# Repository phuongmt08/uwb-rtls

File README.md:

<div align="center">

# UWB-RTLS

### On-device indoor positioning for autonomous mobile robots

**[Results](#experimental-validation) · [System](#system-overview) · [Features](#core-capabilities) · [Quick start](#quick-start) · [Documentation](#documentation)**

</div>

UWB-RTLS is an end-to-end real-time location system developed for indoor mobile robots. Fixed UWB Anchors measure their distance to a mobile Tag using DS-TWR. The Tag validates the ranges, selects a reliable Anchor subset, fuses UWB with IMU data, and calculates its pose directly on an STM32F411. RTLS Studio provides wireless configuration, live diagnostics, visualization, and experiment logging.

<table>
  <tr>
    <th align="center">Best evaluated MAE</th>
    <th align="center">Best evaluated RMSE</th>
    <th align="center">Positioning</th>
    <th align="center">Validation</th>
  </tr>
  <tr>
    <td align="center"><strong>8.5 cm</strong></td>
    <td align="center"><strong>10.9 cm</strong></td>
    <td align="center"><strong>On the Tag</strong></td>
    <td align="center"><strong>2 real environments</strong></td>
  </tr>
</table>

## System Overview

Fixed Anchors provide UWB references around the operating area. The mobile Tag performs ranging and position estimation, sends pose data directly to the vehicle controller, and exposes configuration and telemetry through the BLE gateway.

```mermaid
flowchart TD
    Anchors["Fixed UWB Anchors"] <-->|"DS-TWR ranging"| Tag["Mobile Tag<br/>On-device positioning"]
    Tag -->|"Pose over USB"| Robot["Vehicle Controller"]
    Tag <-->|"Configuration + telemetry"| Gateway["BLE Gateway"]
    Gateway <-->|"USB serial"| Studio["RTLS Studio"]
```

Positioning remains operational without the desktop application: RTLS Studio is a configuration and observability tool, not the positioning engine.

## System in Practice

The experimental platform uses the developed Anchor/Tag hardware and a 1:10-scale vehicle. The photographs below show the actual Chapter 5 test-yard deployment.

<p align="center">
  <br>
  <sub>Full four-Anchor test-yard deployment</sub>
</p>

<table>
  <tr>
    <td width="50%" align="center"><br><sub>Anchor installed at the surveyed height</sub></td>
    <td width="50%" align="center"><br><sub>1:10-scale vehicle carrying the Tag</sub></td>
  </tr>
</table>

RTLS Studio provides the host-side view of the deployed system for device configuration, diagnostics, and experiment recording.

<p align="center">
  <br>
  <sub>Connected-device diagnostics, live logs, and recorded ranging sessions</sub>
</p>

## Experimental Validation

Two dynamic cases were evaluated: a large, mostly line-of-sight test yard and a furnished classroom with stronger multipath and partial obstruction. Direct trilateration and UKF outputs were recorded simultaneously so both estimators saw the same motion and UWB measurements.

### Evaluation protocol

| Item | Method |
|---|---|
| Reference path | Manually surveyed control points connected by interpolation |
| Point error | Euclidean distance from each estimate to the nearest point on the reference path |
| Active interval | Samples before departure and after the vehicle stopped were excluded |
| Repetition | Three runs for each trajectory or Anchor configuration |
| Reported metrics | MAE, RMSE, 95th-percentile error, and maximum error |

### Case 1 — Test yard, four Anchors

The first case used a **9.76 m × 11.64 m** indoor test yard with mostly clear line of sight. Four Anchors surrounded the working area at **0.895 m**, while the Tag was mounted at **0.350 m**. The vehicle followed two surveyed trajectories, each repeated three times.

<table>
  <tr>
    <td width="50%" align="center"></td>
    <td width="50%" align="center"></td>
  </tr>
  <tr>
    <td align="center"><sub>Reference path, direct trilateration, and UKF trajectory</sub></td>
    <td align="center"><sub>Position error from the same representative run</sub></td>
  </tr>
</table>

| Estimator | MAE (m) | RMSE (m) | P95 (m) | Max (m) |
|---|---:|---:|---:|---:|
| Direct trilateration | 0.102 ± 0.006 | 0.134 ± 0.010 | 0.268 ± 0.024 | 0.782 ± 0.281 |
| **UKF** | **0.091 ± 0.005** | **0.117 ± 0.005** | **0.236 ± 0.014** | **0.456 ± 0.063** |

Across the test-yard runs, the UKF reduced average MAE by **10.9%**, RMSE by **12.8%**, and maximum error from **0.782 m to 0.456 m**.

### Case 2 — Classroom, four and six Anchors

The second case used an **8.3 m × 8.7 m** classroom containing desks, people, and reflective surfaces. Anchors were installed at **2.495 m** and the Tag at **0.585 m**. Both four- and six-Anchor layouts were tested to measure the value of additional spatial redundancy.

<table>
  <tr>
    <td width="50%" align="center"></td>
    <td width="50%" align="center"></td>
  </tr>
  <tr>
    <td align="center"><sub>Wall-mounted Anchor</sub></td>
    <td align="center"><sub>Classroom deployment with furniture and occupants</sub></td>
  </tr>
</table>

<table>
  <tr>
    <td width="50%" align="center"></td>
    <td width="50%" align="center"></td>
  </tr>
  <tr>
    <td align="center"><sub>Six-Anchor reference, trilateration, and UKF trajectories</sub></td>
    <td align="center"><sub>Position error from the same representative run</sub></td>
  </tr>
</table>

| Layout | Estimator | MAE (m) | RMSE (m) | P95 (m) | Max (m) |
|---|---|---:|---:|---:|---:|
| 4 Anchors | Direct trilateration | 0.173 ± 0.027 | 0.230 ± 0.037 | 0.457 ± 0.084 | 1.099 ± 0.131 |
| 4 Anchors | **UKF** | **0.139 ± 0.036** | **0.185 ± 0.043** | **0.393 ± 0.085** | **0.583 ± 0.064** |
| 6 Anchors | Direct trilateration | 0.123 ± 0.006 | 0.177 ± 0.007 | 0.340 ± 0.035 | 1.150 ± 0.562 |
| 6 Anchors | **UKF** | **0.085 ± 0.013** | **0.109 ± 0.015** | **0.215 ± 0.035** | **0.340 ± 0.026** |

The six-Anchor UKF configuration produced the strongest overall result: **8.5 cm MAE**, **10.9 cm RMSE**, **21.5 cm P95**, and **34.0 cm maximum error**. The result demonstrates the benefit of additional valid ranging links in a difficult indoor environment.

> **Measurement scope:** the reference trajectory was reconstructed from manually measured control points, not an independent motion-capture system. The results therefore quantify tracking performance under the documented procedure rather than metrology-grade absolute accuracy.

## Core Capabilities

| Area | Implemented capability | Purpose |
|---|---|---|
| Ranging | Asymmetric DS-TWR with TDMA scheduling | Measures multiple Tag-to-Anchor ranges without clock synchronization |
| Measurement validation | Spatial innovation prefilter | Rejects inconsistent range combinations before estimation |
| Anchor selection | Robust precision and WGDOP ranking | Chooses a geometrically useful three-Anchor measurement set |
| Sensor fusion | 8-state UWB/IMU UKF | Estimates planar position, velocity, yaw, and IMU biases |
| Embedded runtime | FreeRTOS task-based firmware | Separates ranging, fusion, communication, storage, and supervision |
| Hardware flexibility | Unified Tag/Anchor STM32 firmware | Selects the device role and Anchor identity without maintaining separate applications |
| Configuration | Persistent profiles with CRC-protected storage | Keeps deployment parameters across resets |
| Communication | Shared Protobuf messages with COBS-framed transport | Maintains one contract across STM32, BLE, and Python |
| Desktop tooling | RTLS Studio and firmware programmer | Supports commissioning, live diagnostics, logs, and updates |

## Hardware and Software

| Layer | Main technology | Responsibility |
|---|---|---|
| Tag and Anchor MCU | STM32F411CEU6, Cortex-M4F | Real-time protocol, positioning, sensor fusion, and interfaces |
| UWB radio | Decawave/Qorvo DW1000 module | Precision packet timestamping for DS-TWR |
| Motion sensor | 6-DOF SPI IMU | Acceleration and yaw-rate input to the UKF |
| BLE nodes | Nordic nRF52 | Wireless configuration and telemetry |
| USB gateway | Nordic nRF52840 dongle | BLE central and USB bridge |
| Embedded OS | FreeRTOS | Deterministic task and queue organization |
| Desktop | Python 3.10+ and PyQt6 | RTLS Studio, programming, and analysis tools |

### Verified Development Environment

| Tool | Verified version |
|---|---|
| STM32CubeIDE | 1.19.0; project supports the 1.10+ workflow |
| Arm GNU Toolchain | 10.3.1 and 13.3.Rel1 |
| GNU Make | 4.4.1 |
| Nordic nRF5 SDK | 17.1.0 |
| Python | 3.10+; 3.12 verified |

## Quick Start

The commands below build the repository and launch RTLS Studio. Device flashing, antenna-delay calibration, Anchor surveying, and commissioning are covered in the [Getting Started Guide](docs/getting_started.md) and [Deployment Guide](docs/deployment.md).

### 1. Clone and generate the shared protocol

```powershell
git clone --recursive https://github.com/phuongmt08/uwb-rtls.git
cd uwb-rtls
make -C protocol
```

### 2. Build the STM32 firmware

Install STM32CubeIDE or an Arm GNU toolchain, then point `GCC_PATH` to its compiler `bin` directory.

```powershell
$env:GCC_PATH = "C:\path\to\arm-none-eabi\bin"
make -C firmware/uwb -j8
```

The build produces ELF, HEX, and BIN files under `firmware/uwb/build`.

### 3. Build the BLE firmware when required

The gateway and BLE bridge targets use Nordic nRF5 SDK 17.1.0.

```powershell
$env:SDK_ROOT = "C:\nRF5_SDK_17.1.0_ddde5a0"
make -C firmware/ble_firmware/central/armgcc
make -C firmware/ble_firmware/peripheral/armgcc
```

### 4. Launch RTLS Studio

```powershell
cd software
python -m venv .venv
.\.venv\Scripts\Activate.ps1
pip install -r requirements.txt
python uwb_rtls_studio/main.py
```

### 5. Commission a deployment

1. Install at least four Anchors around the operating area and assign unique IDs.
2. Survey their coordinates and create the deployment profile in RTLS Studio.
3. Mount the Tag on the vehicle and enter the Tag height.
4. Connect the BLE gateway, select the Tag, and push the configuration.
5. Start ranging and confirm that at least three valid Anchor links are available.
6. Monitor the embedded pose or record a session for offline evaluation.

## Repository Structure

```text
uwb-rtls/
├── firmware/     STM32 application, BLE firmware, and bootloader
├── software/     RTLS Studio, programmer, and analysis tools
├── protocol/     Protobuf contracts and generated bindings
├── hardware/     Schematics, PCB sources, and calibration data
└── docs/         Setup, deployment, architecture, algorithms, and thesis
```

## Documentation

| Start here | Scope |
|---|---|
| **[Getting Started](docs/getting_started.md)** | Toolchains, builds, flashing, and first connection |
| **[Deployment and Commissioning](docs/deployment.md)** | Physical layout, Anchor survey, calibration, and validation |
| **[Firmware Architecture](docs/firmware/architecture.md)** | Embedded layers, RTOS tasks, queues, and runtime ownership |
| **[DS-TWR Ranging Protocol](docs/firmware/ranging_protocol.md)** | Packet sequence, timestamps, timing, and TDMA behavior |
| **[Positioning Algorithms](docs/firmware/positioning_algorithms.md)** | Mathematical model, prefilter, Anchor selection, and UKF |
| **[Schematics and Specifications](docs/hardware/schematics_and_specs.md)** | Hardware boards, interfaces, and design references |
| **[RTLS Studio and Tools](docs/software/rtls_studio_and_tools.md)** | Desktop configuration, monitoring, logging, and programming |
| **[Thesis](docs/thesis/thesis_final.pdf)** | Full design, implementation, and experimental evaluation |

## Team

Developed at the **Faculty of Mechanical Engineering**, Ho Chi Minh City University of Technology and Engineering (**HCMUTE**).

- **Phuong Mai** — Firmware and system architecture
- **Dong Son** — Project co-developer
- **Trung Quan** — Project co-developer

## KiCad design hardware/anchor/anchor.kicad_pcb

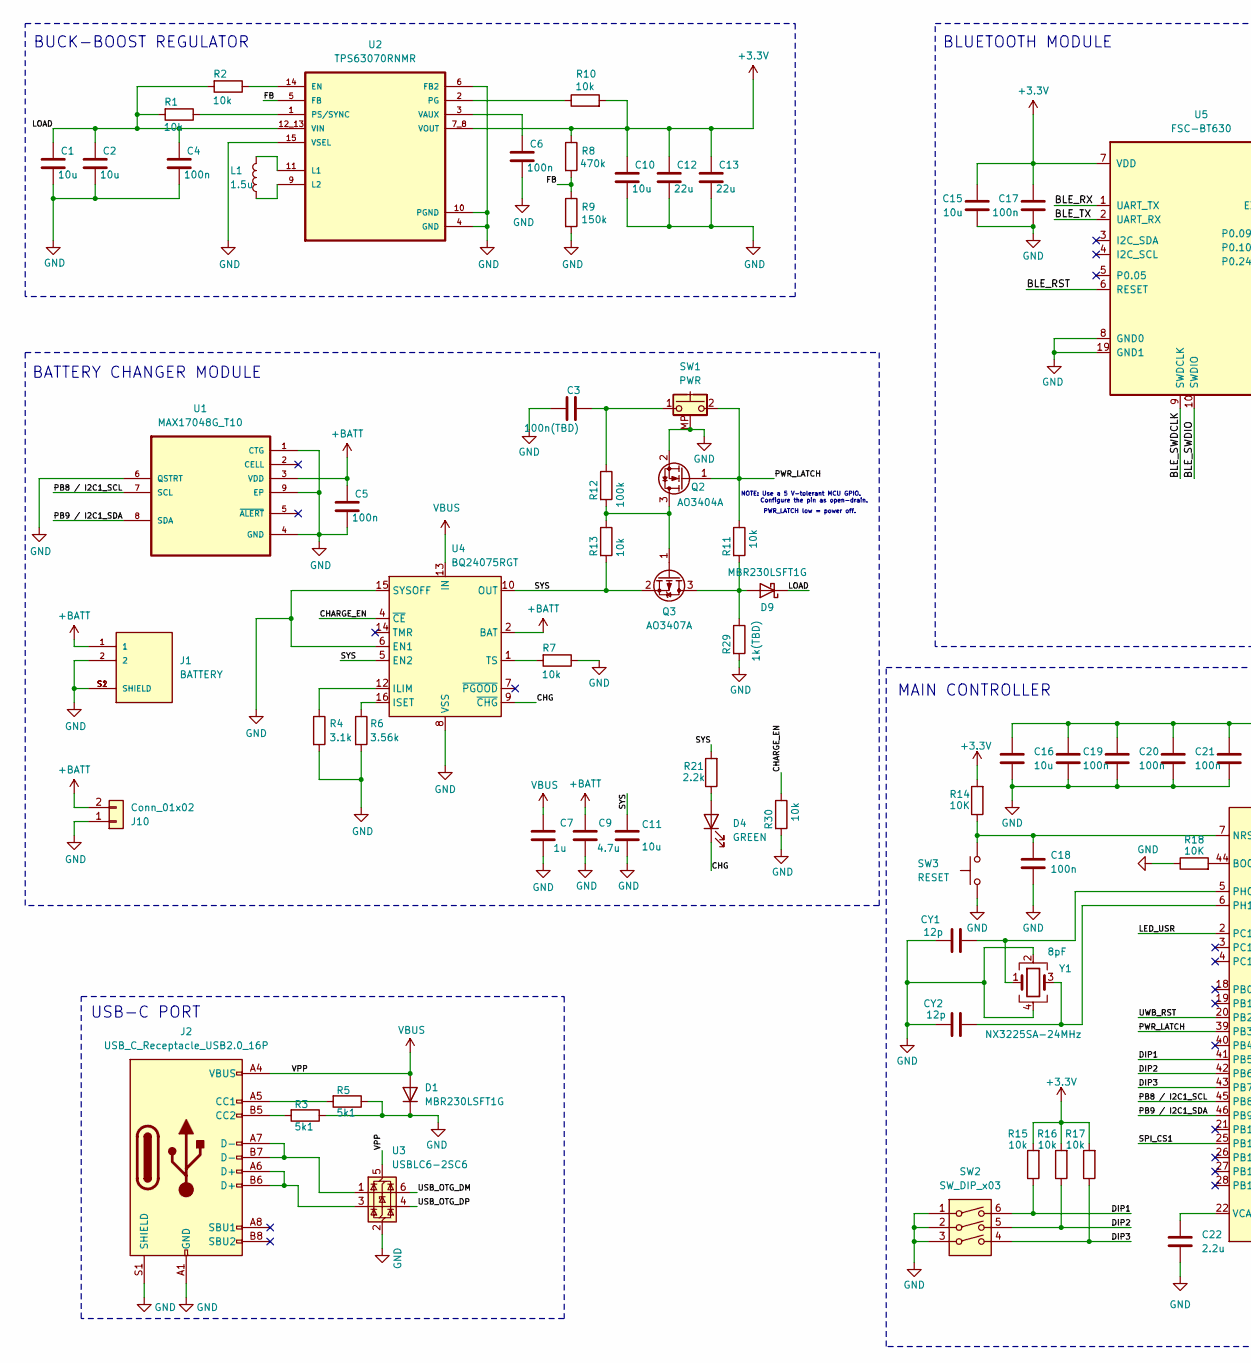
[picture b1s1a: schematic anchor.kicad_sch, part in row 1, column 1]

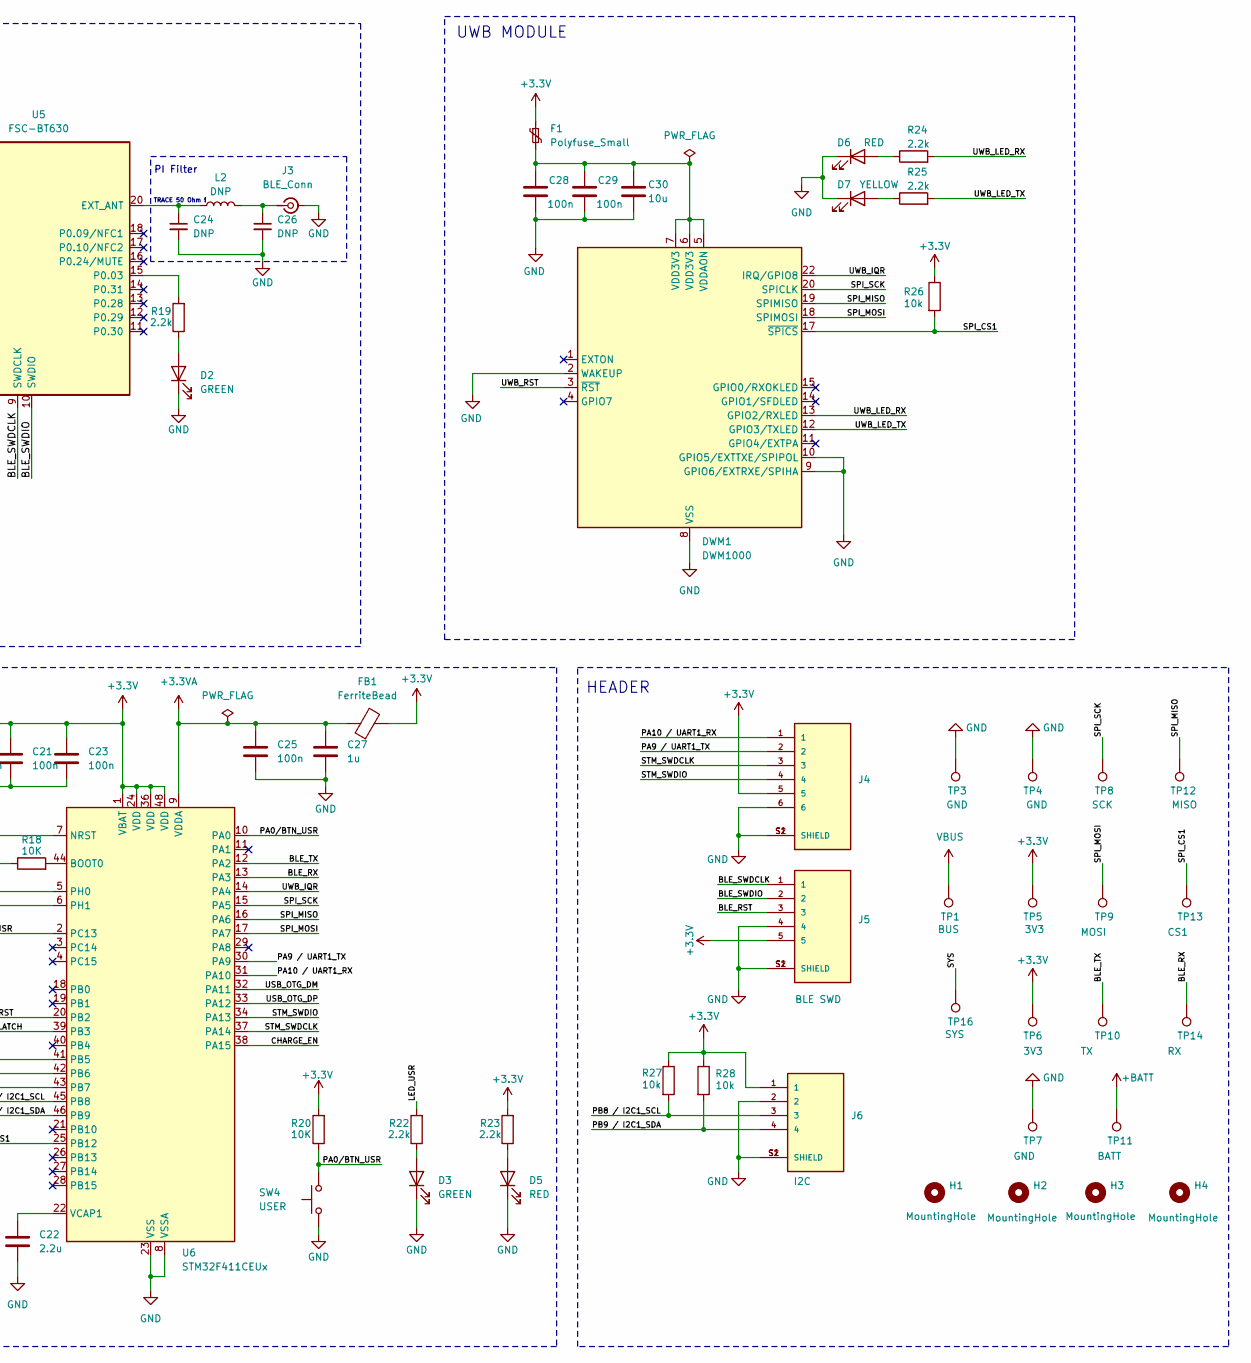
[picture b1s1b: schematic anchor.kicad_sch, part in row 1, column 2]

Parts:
C1, C2, C10, C11: 10u; C_0805_2012Metric
C3: 100n(TBD); C_0603_1608Metric
C4, C5, C6: 100n; C_0603_1608Metric
C7: 1u; C_0805_2012Metric
C9: 4.7u; C_0805_2012Metric
C12, C13: 22u; C_0805_2012Metric
C15, C16, C30: 10u; C_0805_2012Metric_Pad1.18x1.45mm_HandSolder
C17, C18, C19, C20, C21, C23, C25, C28, C29: 100n; C_0603_1608Metric_Pad1.08x0.95mm_HandSolder
C22: 2.2u; C_0805_2012Metric_Pad1.18x1.45mm_HandSolder
C24, C26: DNP; C_0402_1005Metric
C27: 1u; C_0805_2012Metric_Pad1.18x1.45mm_HandSolder
CY1, CY2: 12p; C_0603_1608Metric_Pad1.08x0.95mm_HandSolder
D1: MBR230LSFT1G; D_SOD-323
D2, D3, D4: GREEN; LED_0603_1608Metric_Pad1.05x0.95mm_HandSolder
D5, D6: RED; LED_0603_1608Metric_Pad1.05x0.95mm_HandSolder
D7: YELLOW; LED_0603_1608Metric_Pad1.05x0.95mm_HandSolder
D9: MBR230LSFT1G; D_SOD-123
DWM1: DWM1000
F1: Polyfuse_Small; Fuse_1206_3216Metric
FB1: FerriteBead; L_0603_1608Metric_Pad1.05x0.95mm_HandSolder
H1, H2, H3, H4: MountingHole; MountingHole_2.2mm_M2
J1: BATTERY; JST_BM02B-SRSS-TB_LF__SN_; PARTREV N/A
J2: USB_C_Receptacle_USB2.0_16P; USB_C_Receptacle_HRO_TYPE-C-31-M-12
J3: BLE_Conn; U.FL_Hirose_U.FL-R-SMT-1_Vertical
J4: BM06B-SRSS-TB_LF__SN_; JST_SH_BM06B-SRSS-TB_1x06-1MP_P1.00mm_Vertical; PARTREV N/A
J5: BLE SWD; JST_BM05B-SRSS-TB_LF__SN_; PARTREV N/A
J6: I2C; JST_BM04B-SRSS-TB_LF__SN_; PARTREV N/A
J10: Conn_01x02; SolderWire-0.1sqmm_1x02_P3.6mm_D0.4mm_OD1mm
L1: 1.5u; L_Sunlord_SWPA4020S
L2: DNP; L_0402_1005Metric
Q2: AO3404A; SOT-23
Q3: AO3407A; SOT-23
R1, R2, R7, R10, R11, R13, R30: 10k; R_0603_1608Metric
R3, R5: 5k1; R_0603_1608Metric_Pad0.98x0.95mm_HandSolder
R4: 3.1k; R_0603_1608Metric
R6: 3.56k; R_0603_1608Metric
R8: 470k; R_0805_2012Metric_Pad1.20x1.40mm_HandSolder
R9: 150k; R_0805_2012Metric_Pad1.20x1.40mm_HandSolder
R12: 100k; R_0603_1608Metric
R14, R18, R20: 10K; R_0603_1608Metric_Pad0.98x0.95mm_HandSolder
R15, R16, R17, R26, R27, R28: 10k; R_0603_1608Metric_Pad0.98x0.95mm_HandSolder
R19, R22, R23, R24, R25: 2.2k; R_0603_1608Metric_Pad0.98x0.95mm_HandSolder
R21: 2.2k; R_0603_1608Metric
R29: 1k(TBD); R_0603_1608Metric
SW1: PWR; SW_Push_1P1T-MP_NO_Horizontal_Alps_SKRTLAE010
SW2: SW_DIP_x03; SW_DIP_SPSTx03_Slide_KingTek_DSHP03TJ_W5.25mm_P1.27mm_JPin
SW3: RESET; SW_Tactile_SMD_3x4mm_2pin_update
SW4: USER; SW_Tactile_SMD_3x4mm_2pin_update
TP1: BUS; TestPoint_Pad_D1.5mm
TP3, TP7: GND; TestPoint_Pad_D1.5mm
TP4: GND; TestPoint_Pad_1.0x1.0mm
TP5, TP6: 3V3; TestPoint_Pad_D1.5mm
TP8: SCK; TestPoint_Pad_D1.0mm
TP9: MOSI; TestPoint_Pad_D1.0mm
TP10: TX; TestPoint_Pad_D1.0mm
TP11: BATT; TestPoint_Pad_D1.5mm
TP12: MISO; TestPoint_Pad_D1.0mm
TP13: CS1; TestPoint_Pad_D1.0mm
TP14: RX; TestPoint_Pad_D1.0mm
TP16: SYS; TestPoint_Pad_D1.5mm
U1: MAX17048G_T10; SON-8-1EP_3x2mm_P0.5mm_EP1.4x1.6mm
U2: TPS63070RNMR; VREG_TPS63070RNMR
U3: USBLC6-2SC6; SOT-23-6
U4: BQ24075RGT; VQFN-16-1EP_3x3mm_P0.5mm_EP1.6x1.6mm
U5: FSC-BT630
U6: STM32F411CEUx; QFN-48-1EP_7x7mm_P0.5mm_EP5.6x5.6mm
Y1: NX3225SA-24MHz; Crystal_SMD_3225-4Pin_3.2x2.5mm

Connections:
+3.3V: C10.1, C12.1, C13.1, C15.1, C16.1, C17.1, C19.1, C20.1, C21.1, C23.1, F1.1, FB1.2, J4.5, J5.5, J6.1, R8.1, R10.2, R14.2, R15.2, R16.2, R17.2, R20.2, R23.2, R26.1, R27.1, R28.1, TP5.1, TP6.1, U2.7_8 (VOUT), U5.7 (VDD), U6.1 (VBAT), U6.24 (VDD), U6.36 (VDD), U6.48 (VDD)
+3.3VA: C25.1, C27.1, FB1.1, U6.9 (VDDA)
+BATT: C5.1, C9.1, J1.1, J10.2, TP11.1, U1.3 (VDD), U4.2 (BAT), U4.3 (BAT)
/BLE_RST: J5.3, U5.6 (RESET)
/BLE_RX: TP14.1, U5.1 (UART_TX), U6.13 (PA3)
/BLE_SWDCLK: J5.1, U5.9 (SWDCLK)
/BLE_SWDIO: J5.2, U5.10 (SWDIO)
/BLE_TX: TP10.1, U5.2 (UART_RX), U6.12 (PA2)
/CHARGE_EN: R30.1, U4.4 (~CE), U6.38 (PA15)
/CHG: D4.1 (K), U4.9 (~CHG)
/DIP1: R15.1, SW2.6, U6.41 (PB5)
/DIP2: R16.1, SW2.5, U6.42 (PB6)
/DIP3: R17.1, SW2.4, U6.43 (PB7)
/FB: R8.2, R9.1, U2.5 (FB)
/LED_USR: R22.2, U6.2 (PC13)
/LOAD: C1.1, C2.1, C4.1, D9.1 (K), R1.2, R2.2, U2.12_13 (VIN)
/PA0/BTN_USR: R20.1, SW4.2, U6.10 (PA0)
/PA9 / UART1_TX: J4.2, U6.30 (PA9)
/PA10 / UART1_RX: J4.1, U6.31 (PA10)
/PB8 / I2C1_SCL: J6.3, R27.2, U1.7 (SCL), U6.45 (PB8)
/PB9 / I2C1_SDA: J6.4, R28.2, U1.8 (SDA), U6.46 (PB9)
/PWR_LATCH: Q2.1 (G), R11.1, SW1.2, U6.39 (PB3)
/SPI_CS1: DWM1.17 (~SPICS), R26.2, TP13.1, U6.25 (PB12)
/SPI_MISO: DWM1.19 (SPIMISO), TP12.1, U6.16 (PA6)
/SPI_MOSI: DWM1.18 (SPIMOSI), TP9.1, U6.17 (PA7)
/SPI_SCK: DWM1.20 (SPICLK), TP8.1, U6.15 (PA5)
/STM_SWDCLK: J4.3, U6.37 (PA14)
/STM_SWDIO: J4.4, U6.34 (PA13)
/SYS: C11.1, Q3.2 (S), R13.2, R21.2, TP16.1, U4.5 (EN2), U4.10 (OUT), U4.11 (OUT)
/USB_OTG_DM: U3.6 (I/O1), U6.32 (PA11)
/USB_OTG_DP: U3.4 (I/O2), U6.33 (PA12)
/UWB_IQR: DWM1.22 (IRQ/GPIO8), U6.14 (PA4)
/UWB_LED_RX: DWM1.13 (GPIO2/RXLED), R24.2
/UWB_LED_TX: DWM1.12 (GPIO3/TXLED), R25.2
/UWB_RST: DWM1.3 (~RST), U6.20 (PB2)
GND: C1.2, C2.2, C3.1, C4.2, C5.2, C6.2, C7.1, C9.2, C10.2, C11.2, C12.2, C13.2, C15.2, C16.2, C17.2, C18.2, C19.2, C20.2, C21.2, C22.2, C23.2, C24.2, C25.2, C26.2, C27.2, C28.2, C29.2, C30.2, CY1.1, CY2.1, D1.1 (K), D2.1 (K), D3.1 (K), D5.1 (K), D6.1 (K), D7.1 (K), DWM1.2 (WAKEUP), DWM1.8 (VSS), DWM1.9 (GPIO6/EXTRXE/SPIHA), DWM1.10 (GPIO5/EXTTXE/SPIPOL), DWM1.16 (VSS), DWM1.21 (VSS), DWM1.23 (VSS), DWM1.24 (VSS), J1.2, J1.S1 (SHIELD), J1.S2 (SHIELD), J2.A1 (GND), J2.A12 (GND), J2.B1 (GND), J2.B12 (GND), J2.S1 (SHIELD), J3.2 (Ext), J4.6, J4.S1 (SHIELD), J4.S2 (SHIELD), J5.4, J5.S1 (SHIELD), J5.S2 (SHIELD), J6.2, J6.S1 (SHIELD), J6.S2 (SHIELD), J10.1, Q2.2 (S), R3.1, R4.2, R5.1, R6.2, R7.1, R9.2, R18.1, R29.2, R30.2, SW1.MP (B), SW2.1, SW2.2, SW2.3, SW3.1, SW4.1, TP3.1, TP4.1, TP7.1, U1.1 (CTG), U1.4 (GND), U1.6 (QSTRT), U1.9 (EP), U2.4 (GND), U2.6 (FB2), U2.10 (PGND), U2.15 (VSEL), U3.2 (GND), U4.6 (EN1), U4.8 (VSS), U4.15 (SYSOFF), U4.17 (VSS), U5.8 (GND0), U5.19 (GND1), U6.8 (VSSA), U6.23 (VSS), U6.35 (VSS), U6.47 (VSS), U6.49 (VSS), Y1.2, Y1.4
unnamed: C3.2, R12.1, SW1.1
unnamed: D2.2 (A), R19.1
unnamed: D3.2 (A), R22.1
unnamed: D4.2 (A), R21.1
unnamed: D5.2 (A), R23.1
unnamed: D6.2 (A), R24.1
unnamed: D7.2 (A), R25.1
unnamed: D9.2 (A), Q3.3 (D), R11.2, R29.1
unnamed: C28.1, C29.1, C30.1, DWM1.5 (VDDAON), DWM1.6 (VDD3V3), DWM1.7 (VDD3V3), F1.2
unnamed: J2.A5 (CC1), R5.2
unnamed: J2.B5 (CC2), R3.2
unnamed: J2.A6 (D+), J2.B6 (D+), U3.3 (I/O2)
unnamed: J2.A7 (D-), J2.B7 (D-), U3.1 (I/O1)
unnamed: C26.1, J3.1 (In), L2.2
unnamed: Q2.3 (D), Q3.1 (G), R12.2, R13.1
unnamed: R2.1, U2.14 (EN)
unnamed: L1.2, U2.11 (L1)
unnamed: L1.1, U2.9 (L2)
unnamed: R10.1, U2.2 (PG)
unnamed: R1.1, U2.1 (PS/SYNC)
unnamed: C6.1, U2.3 (VAUX)
unnamed: R4.1, U4.12 (ILIM)
unnamed: R6.1, U4.16 (ISET)
unnamed: R7.2, U4.1 (TS)
unnamed: C24.1, L2.1, U5.20 (EXT_ANT)
unnamed: R19.2, U5.15 (P0.03)
unnamed: R18.2, U6.44 (BOOT0)
unnamed: C18.1, R14.1, SW3.2, U6.7 (NRST)
unnamed: CY1.2, U6.5 (PH0), Y1.1
unnamed: CY2.2, U6.6 (PH1), Y1.3
unnamed: C22.1, U6.22 (VCAP1)
VBUS: C7.2, D1.2 (A), J2.A4 (VBUS), J2.A9 (VBUS), J2.B4 (VBUS), J2.B9 (VBUS), TP1.1, U3.5 (VBUS), U4.13 (IN)

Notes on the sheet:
BLUETOOTH MODULE
USB-C PORT
MAIN CONTROLLER
HEADER
BATTERY CHANGER MODULE
UWB MODULE
BUCK-BOOST REGULATOR
PI Filter
NOTE: Use a 5 V-tolerant MCU GPIO. Configure the pin as open-drain.
TRACE 50 Ohm !
PWR_LATCH low = power off.

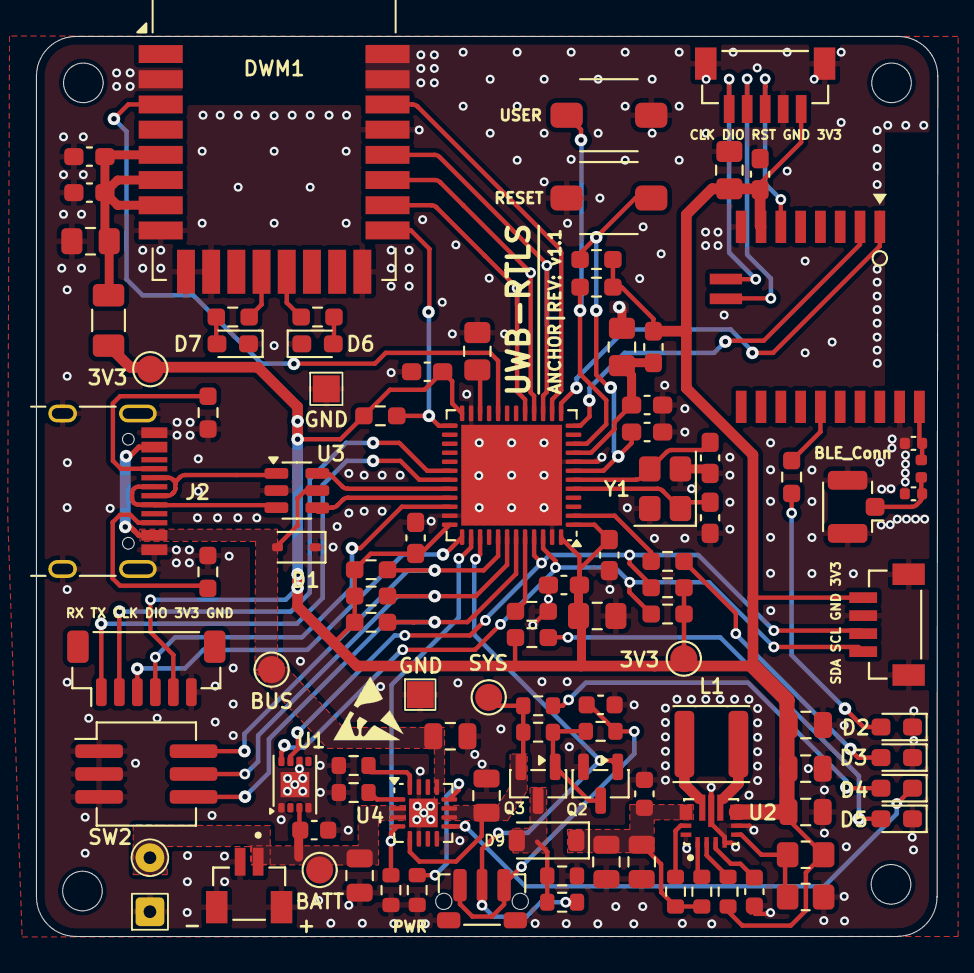
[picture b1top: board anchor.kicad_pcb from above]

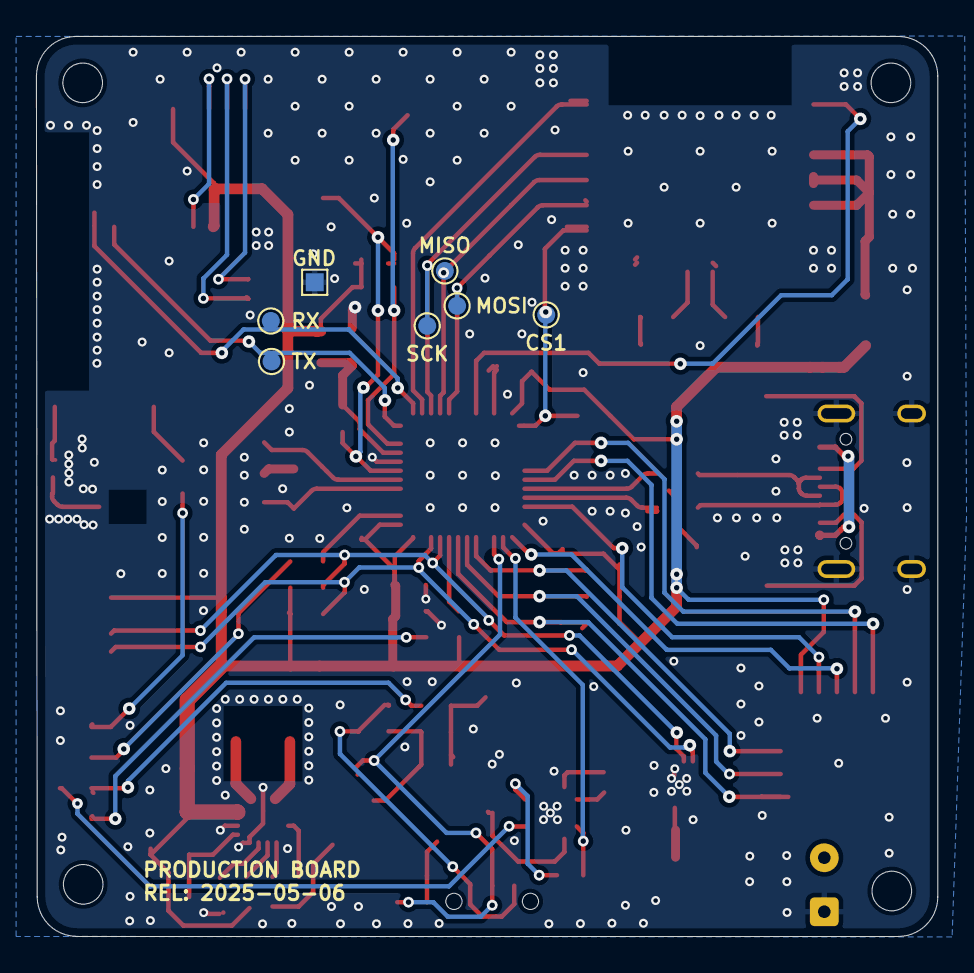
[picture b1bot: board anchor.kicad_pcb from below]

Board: 2 copper layers, 50.1 x 50.0 mm, 111 parts (8 on the bottom side), 68 nets.

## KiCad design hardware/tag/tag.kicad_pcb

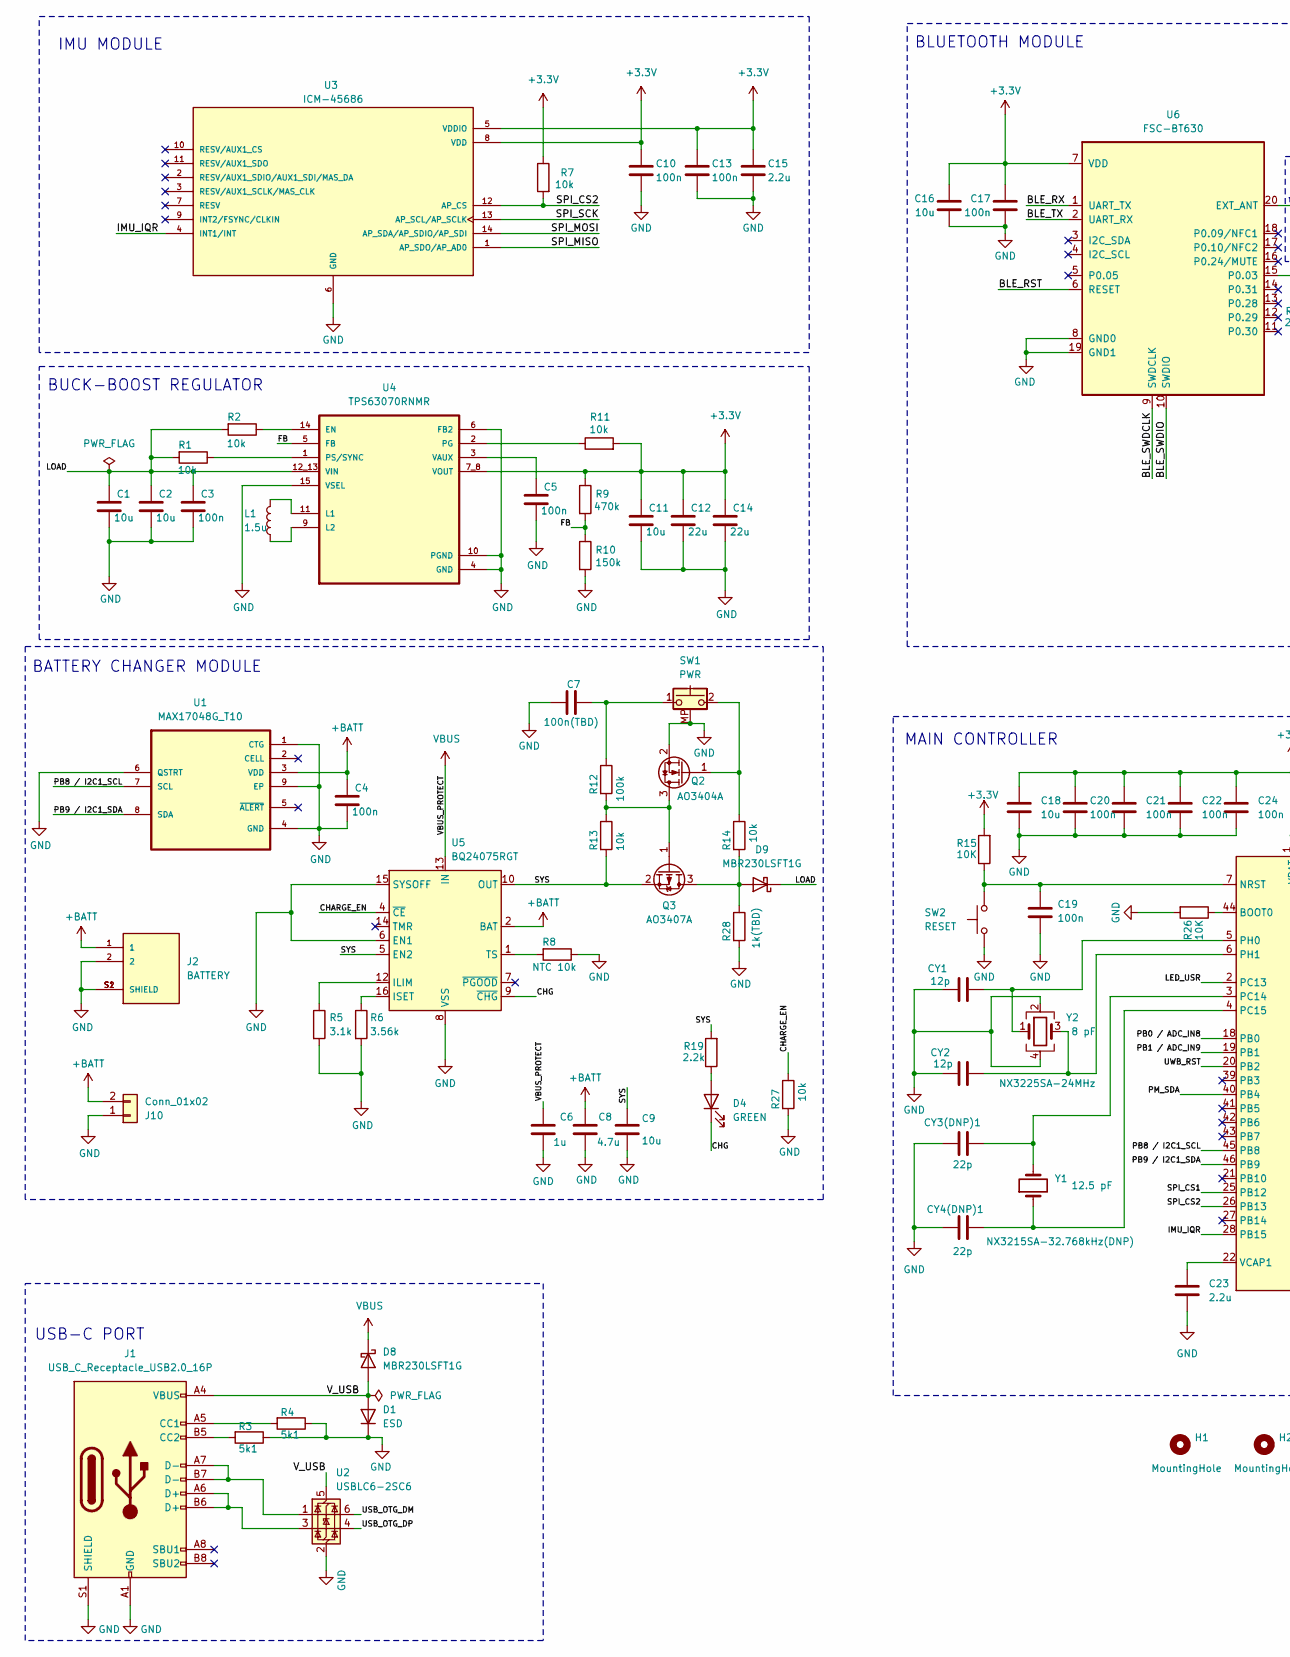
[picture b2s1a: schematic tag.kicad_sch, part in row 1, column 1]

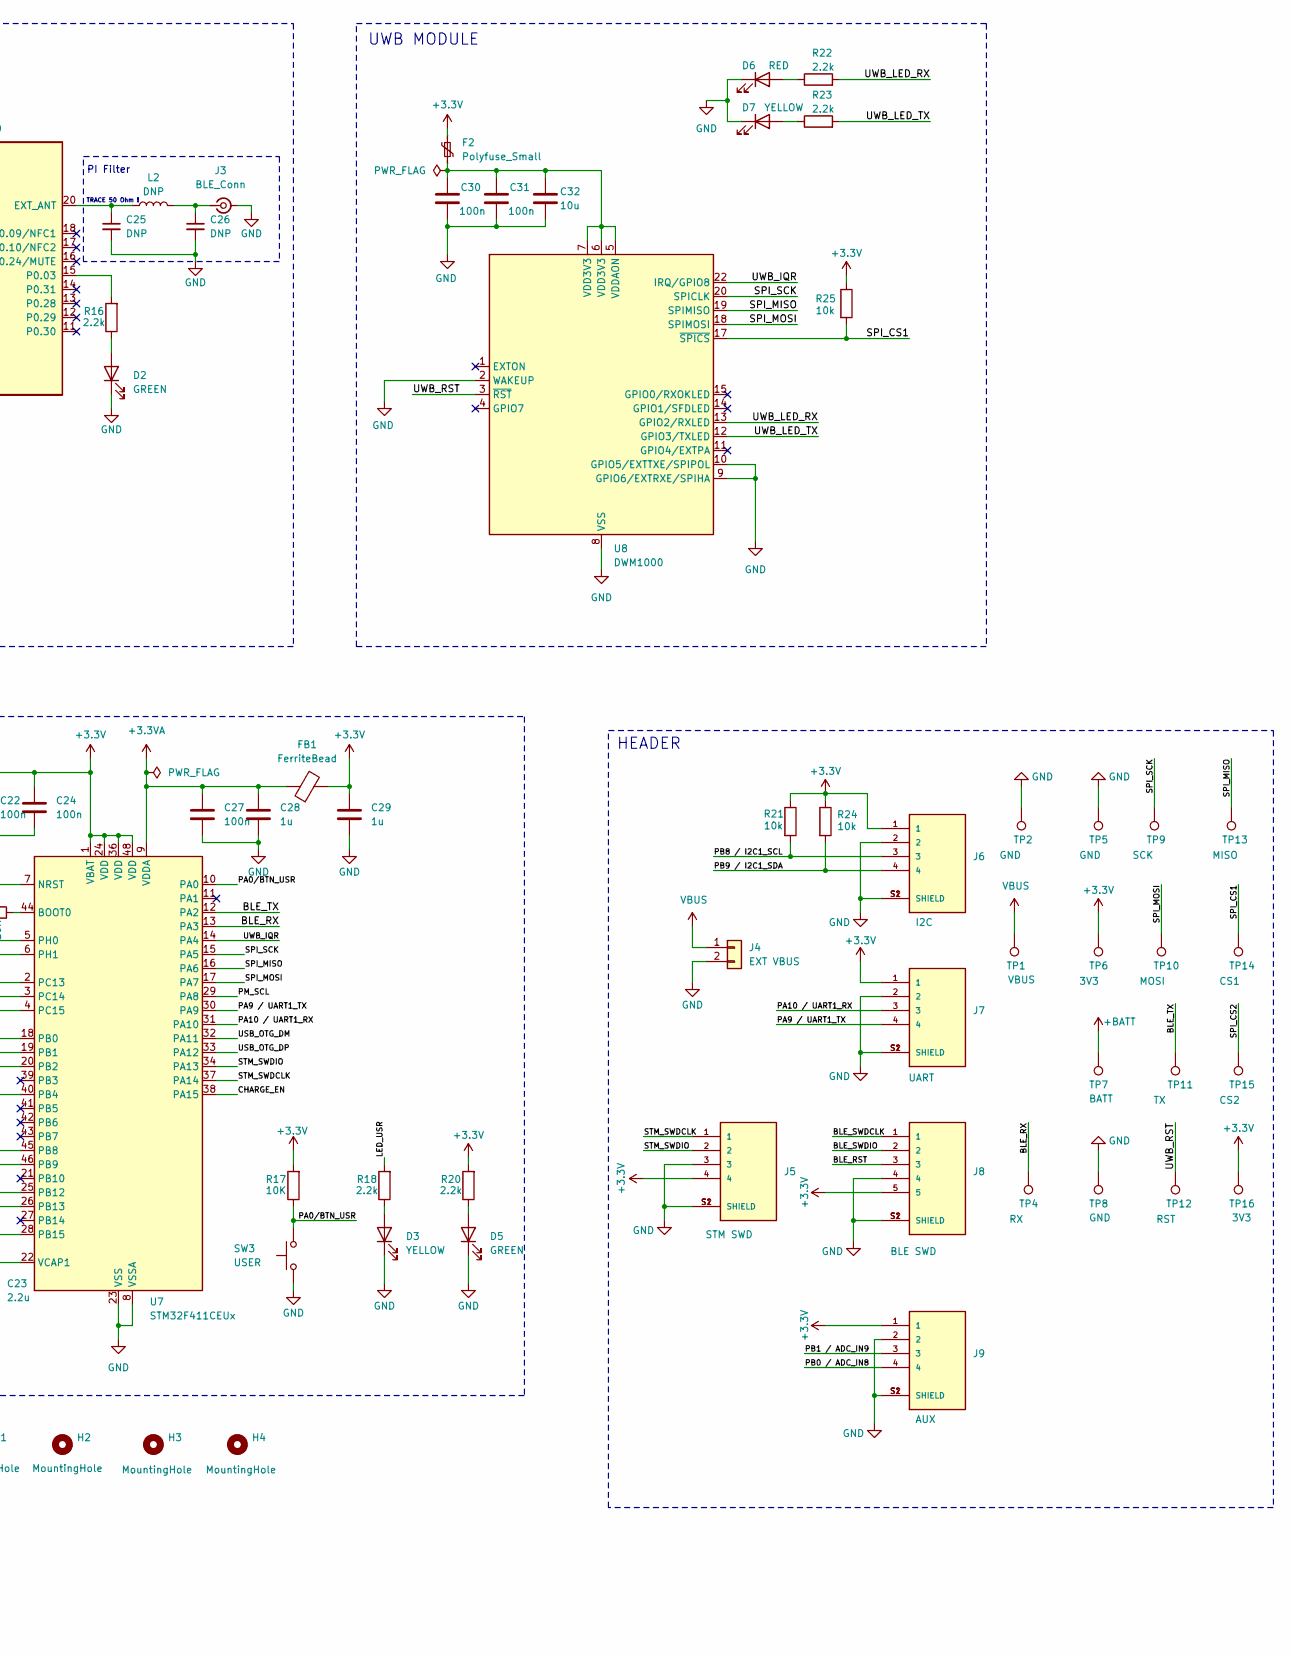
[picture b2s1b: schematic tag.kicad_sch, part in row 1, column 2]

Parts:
C1, C2, C9, C11: 10u; C_0805_2012Metric
C3, C4, C5: 100n; C_0603_1608Metric
C6: 1u; C_0805_2012Metric
C7: 100n(TBD); C_0603_1608Metric
C8: 4.7u; C_0805_2012Metric
C10, C13, C17, C19, C20, C21, C22, C24, C27, C30, C31: 100n; C_0603_1608Metric_Pad1.08x0.95mm_HandSolder
C12, C14: 22u; C_0805_2012Metric
C15, C23: 2.2u; C_0805_2012Metric_Pad1.18x1.45mm_HandSolder
C16, C18, C32: 10u; C_0805_2012Metric_Pad1.18x1.45mm_HandSolder
C25, C26: DNP; C_0402_1005Metric
C28, C29: 1u; C_0805_2012Metric_Pad1.18x1.45mm_HandSolder
CY1, CY2: 12p; C_0603_1608Metric_Pad1.08x0.95mm_HandSolder
CY3(DNP)1, CY4(DNP)1: 22p; C_0603_1608Metric_Pad1.08x0.95mm_HandSolder
D1: ESD; D_SOD-323
D2, D4, D5: GREEN; LED_0603_1608Metric_Pad1.05x0.95mm_HandSolder
D3, D7: YELLOW; LED_0603_1608Metric_Pad1.05x0.95mm_HandSolder
D6: RED; LED_0603_1608Metric_Pad1.05x0.95mm_HandSolder
D8: MBR230LSFT1G; D_SOD-123F
D9: MBR230LSFT1G; D_SOD-123
F2: Polyfuse_Small; Fuse_1206_3216Metric
FB1: FerriteBead; L_0603_1608Metric_Pad1.05x0.95mm_HandSolder
H1, H2, H3, H4: MountingHole; MountingHole_2.2mm_M2
J1: USB_C_Receptacle_USB2.0_16P; USB_C_Receptacle_HRO_TYPE-C-31-M-12
J2: BATTERY; JST_BM02B-SRSS-TB_LF__SN_; PARTREV N/A
J3: BLE_Conn; U.FL_Hirose_U.FL-R-SMT-1_Vertical
J4: EXT VBUS
J5: STM SWD; JST_BM04B-SRSS-TB_LF__SN_; PARTREV N/A
J6: I2C; JST_BM04B-SRSS-TB_LF__SN_; PARTREV N/A
J7: UART; JST_BM04B-SRSS-TB_LF__SN_; PARTREV N/A
J8: BLE SWD; JST_BM05B-SRSS-TB_LF__SN_; PARTREV N/A
J9: AUX; JST_BM04B-SRSS-TB_LF__SN_; PARTREV N/A
J10: Conn_01x02; SolderWire-0.1sqmm_1x02_P3.6mm_D0.4mm_OD1mm
L1: 1.5u; L_Sunlord_SWPA4020S
L2: DNP; L_0402_1005Metric
Q2: AO3404A; SOT-23
Q3: AO3407A; SOT-23
R1, R2, R11, R13, R14, R27: 10k; R_0603_1608Metric
R3, R4: 5k1; R_0603_1608Metric_Pad0.98x0.95mm_HandSolder
R5: 3.1k; R_0603_1608Metric
R6: 3.56k; R_0603_1608Metric
R7, R21, R24, R25: 10k; R_0603_1608Metric_Pad0.98x0.95mm_HandSolder
R8: NTC 10k; R_0603_1608Metric
R9: 470k; R_0805_2012Metric_Pad1.20x1.40mm_HandSolder
R10: 150k; R_0805_2012Metric_Pad1.20x1.40mm_HandSolder
R12: 100k; R_0603_1608Metric
R15, R17, R26: 10K; R_0603_1608Metric_Pad0.98x0.95mm_HandSolder
R16, R18, R20, R22, R23: 2.2k; R_0603_1608Metric_Pad0.98x0.95mm_HandSolder
R19: 2.2k; R_0603_1608Metric
R28: 1k(TBD); R_0603_1608Metric
SW1: PWR; SW_Push_1P1T-MP_NO_Horizontal_Alps_SKRTLAE010
SW2: RESET; SW_Tactile_SMD_3x4mm_2pin_update
SW3: USER; SW_Tactile_SMD_3x4mm_2pin_update
TP1: VBUS; TestPoint_Pad_D1.5mm
TP2, TP5: GND; TestPoint_Pad_1.5x1.5mm
TP4: RX; TestPoint_Pad_D1.0mm
TP6, TP16: 3V3; TestPoint_Pad_D1.5mm
TP7: BATT; TestPoint_Pad_D1.5mm
TP8: GND; TestPoint_Pad_1.0x1.0mm
TP9: SCK; TestPoint_Pad_D1.0mm
TP10: MOSI; TestPoint_Pad_D1.0mm
TP11: TX; TestPoint_Pad_D1.0mm
TP12: RST; TestPoint_Pad_D1.0mm
TP13: MISO; TestPoint_Pad_D1.0mm
TP14: CS1; TestPoint_Pad_D1.0mm
TP15: CS2; TestPoint_Pad_D1.0mm
U1: MAX17048G_T10; SON-8-1EP_3x2mm_P0.5mm_EP1.4x1.6mm
U2: USBLC6-2SC6; SOT-23-6
U3: ICM-45686; IC_ICM-45686; PARTREV 0.2
U4: TPS63070RNMR; VREG_TPS63070RNMR
U5: BQ24075RGT; VQFN-16-1EP_3x3mm_P0.5mm_EP1.6x1.6mm
U6: FSC-BT630
U7: STM32F411CEUx; QFN-48-1EP_7x7mm_P0.5mm_EP5.6x5.6mm
U8: DWM1000
Y1: NX3215SA-32.768kHz(DNP); Crystal_SMD_3215-2Pin_3.2x1.5mm
Y2: NX3225SA-24MHz; Crystal_SMD_3225-4Pin_3.2x2.5mm

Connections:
+3.3V: C10.1, C11.1, C12.1, C13.1, C14.1, C15.1, C16.1, C17.1, C18.1, C20.1, C21.1, C22.1, C24.1, C29.1, F2.1, FB1.2, J5.4, J6.1, J7.1, J8.5, J9.1, R7.1, R9.1, R11.2, R15.2, R17.2, R20.2, R21.1, R24.1, R25.1, TP6.1, TP16.1, U3.5 (VDDIO), U3.8 (VDD), U4.7_8 (VOUT), U6.7 (VDD), U7.1 (VBAT), U7.24 (VDD), U7.36 (VDD), U7.48 (VDD)
+3.3VA: C27.1, C28.1, FB1.1, U7.9 (VDDA)
+BATT: C4.1, C8.1, J2.1, J10.2, TP7.1, U1.3 (VDD), U5.2 (BAT), U5.3 (BAT)
/BLE_RST: J8.3, U6.6 (RESET)
/BLE_RX: TP4.1, U6.1 (UART_TX), U7.13 (PA3)
/BLE_SWDCLK: J8.1, U6.9 (SWDCLK)
/BLE_SWDIO: J8.2, U6.10 (SWDIO)
/BLE_TX: TP11.1, U6.2 (UART_RX), U7.12 (PA2)
/CHARGE_EN: R27.1, U5.4 (~CE), U7.38 (PA15)
/CHG: D4.1 (K), U5.9 (~CHG)
/FB: R9.2, R10.1, U4.5 (FB)
/IMU_IQR: U3.4 (INT1/INT), U7.28 (PB15)
/LED_USR: R18.2, U7.2 (PC13)
/LOAD: C1.1, C2.1, C3.1, D9.1 (K), R1.2, R2.2, U4.12_13 (VIN)
/PA0/BTN_USR: R17.1, SW3.2, U7.10 (PA0)
/PA9 / UART1_TX: J7.4, U7.30 (PA9)
/PA10 / UART1_RX: J7.3, U7.31 (PA10)
/PB0 / ADC_IN8: J9.4, U7.18 (PB0)
/PB1 / ADC_IN9: J9.3, U7.19 (PB1)
/PB8 / I2C1_SCL: J6.3, R21.2, U1.7 (SCL), U7.45 (PB8)
/PB9 / I2C1_SDA: J6.4, R24.2, U1.8 (SDA), U7.46 (PB9)
/PM_SCL: U7.29 (PA8)
/PM_SDA: U7.40 (PB4)
/SPI_CS1: R25.2, TP14.1, U7.25 (PB12), U8.17 (~SPICS)
/SPI_CS2: R7.2, TP15.1, U3.12 (AP_CS), U7.26 (PB13)
/SPI_MISO: TP13.1, U3.1 (AP_SDO/AP_AD0), U7.16 (PA6), U8.19 (SPIMISO)
/SPI_MOSI: TP10.1, U3.14 (AP_SDA/AP_SDIO/AP_SDI), U7.17 (PA7), U8.18 (SPIMOSI)
/SPI_SCK: TP9.1, U3.13 (AP_SCL/AP_SCLK), U7.15 (PA5), U8.20 (SPICLK)
/STM_SWDCLK: J5.1, U7.37 (PA14)
/STM_SWDIO: J5.2, U7.34 (PA13)
/SYS: C9.1, Q3.2 (S), R13.2, R19.2, U5.5 (EN2), U5.10 (OUT), U5.11 (OUT)
/USB_OTG_DM: U2.6 (I/O1), U7.32 (PA11)
/USB_OTG_DP: U2.4 (I/O2), U7.33 (PA12)
/UWB_IQR: U7.14 (PA4), U8.22 (IRQ/GPIO8)
/UWB_LED_RX: R22.2, U8.13 (GPIO2/RXLED)
/UWB_LED_TX: R23.2, U8.12 (GPIO3/TXLED)
/UWB_RST: TP12.1, U7.20 (PB2), U8.3 (~RST)
/V_USB: D1.2 (A), D8.2 (A), J1.A4 (VBUS), J1.A9 (VBUS), J1.B4 (VBUS), J1.B9 (VBUS), U2.5 (VBUS)
GND: C1.2, C2.2, C3.2, C4.2, C5.2, C6.1, C7.1, C8.2, C9.2, C10.2, C11.2, C12.2, C13.2, C14.2, C15.2, C16.2, C17.2, C18.2, C19.2, C20.2, C21.2, C22.2, C23.2, C24.2, C25.2, C26.2, C27.2, C28.2, C29.2, C30.2, C31.2, C32.2, CY1.1, CY2.1, CY3(DNP)1.1, CY4(DNP)1.1, D1.1 (K), D2.1 (K), D3.1 (K), D5.1 (K), D6.1 (K), D7.1 (K), J1.A1 (GND), J1.A12 (GND), J1.B1 (GND), J1.B12 (GND), J1.S1 (SHIELD), J2.2, J2.S1 (SHIELD), J2.S2 (SHIELD), J3.2 (Ext), J4.2, J5.3, J5.S1 (SHIELD), J5.S2 (SHIELD), J6.2, J6.S1 (SHIELD), J6.S2 (SHIELD), J7.2, J7.S1 (SHIELD), J7.S2 (SHIELD), J8.4, J8.S1 (SHIELD), J8.S2 (SHIELD), J9.2, J9.S1 (SHIELD), J9.S2 (SHIELD), J10.1, Q2.2 (S), R3.1, R4.1, R5.2, R6.2, R8.1, R10.2, R26.2, R27.2, R28.2, SW1.MP (B), SW2.1, SW3.1, TP2.1, TP5.1, TP8.1, U1.1 (CTG), U1.4 (GND), U1.6 (QSTRT), U1.9 (EP), U2.2 (GND), U3.6 (GND), U4.4 (GND), U4.6 (FB2), U4.10 (PGND), U4.15 (VSEL), U5.6 (EN1), U5.8 (VSS), U5.15 (SYSOFF), U5.17 (VSS), U6.8 (GND0), U6.19 (GND1), U7.8 (VSSA), U7.23 (VSS), U7.35 (VSS), U7.47 (VSS), U7.49 (VSS), U8.2 (WAKEUP), U8.8 (VSS), U8.9 (GPIO6/EXTRXE/SPIHA), U8.10 (GPIO5/EXTTXE/SPIPOL), U8.16 (VSS), U8.21 (VSS), U8.23 (VSS), U8.24 (VSS), Y2.2, Y2.4
unnamed: C7.2, R12.1, SW1.1
unnamed: D2.2 (A), R16.1
unnamed: D3.2 (A), R18.1
unnamed: D4.2 (A), R19.1
unnamed: D5.2 (A), R20.1
unnamed: D6.2 (A), R22.1
unnamed: D7.2 (A), R23.1
unnamed: D9.2 (A), Q3.3 (D), R14.2, R28.1
unnamed: J1.A5 (CC1), R4.2
unnamed: J1.B5 (CC2), R3.2
unnamed: J1.A6 (D+), J1.B6 (D+), U2.3 (I/O2)
unnamed: J1.A7 (D-), J1.B7 (D-), U2.1 (I/O1)
unnamed: C26.1, J3.1 (In), L2.2
unnamed: Q2.3 (D), Q3.1 (G), R12.2, R13.1
unnamed: R2.1, U4.14 (EN)
unnamed: L1.2, U4.11 (L1)
unnamed: L1.1, U4.9 (L2)
unnamed: R11.1, U4.2 (PG)
unnamed: R1.1, U4.1 (PS/SYNC)
unnamed: C5.1, U4.3 (VAUX)
unnamed: R5.1, U5.12 (ILIM)
unnamed: R6.1, U5.16 (ISET)
unnamed: R8.2, U5.1 (TS)
unnamed: C25.1, L2.1, U6.20 (EXT_ANT)
unnamed: R16.2, U6.15 (P0.03)
unnamed: R26.1, U7.44 (BOOT0)
unnamed: C19.1, R15.1, SW2.2, U7.7 (NRST)
unnamed: CY3(DNP)1.2, U7.3 (PC14), Y1.2
unnamed: CY4(DNP)1.2, U7.4 (PC15), Y1.1
unnamed: CY1.2, U7.5 (PH0), Y2.1
unnamed: CY2.2, U7.6 (PH1), Y2.3
unnamed: C23.1, U7.22 (VCAP1)
unnamed: C30.1, C31.1, C32.1, F2.2, U8.5 (VDDAON), U8.6 (VDD3V3), U8.7 (VDD3V3)
VBUS: C6.2, D8.1 (K), J4.1, TP1.1, U5.13 (IN)

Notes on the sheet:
TRACE 50 Ohm !
PI Filter
BATTERY CHANGER MODULE
MAIN CONTROLLER
IMU MODULE
HEADER
USB-C PORT
BUCK-BOOST REGULATOR
BLUETOOTH MODULE
UWB MODULE

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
